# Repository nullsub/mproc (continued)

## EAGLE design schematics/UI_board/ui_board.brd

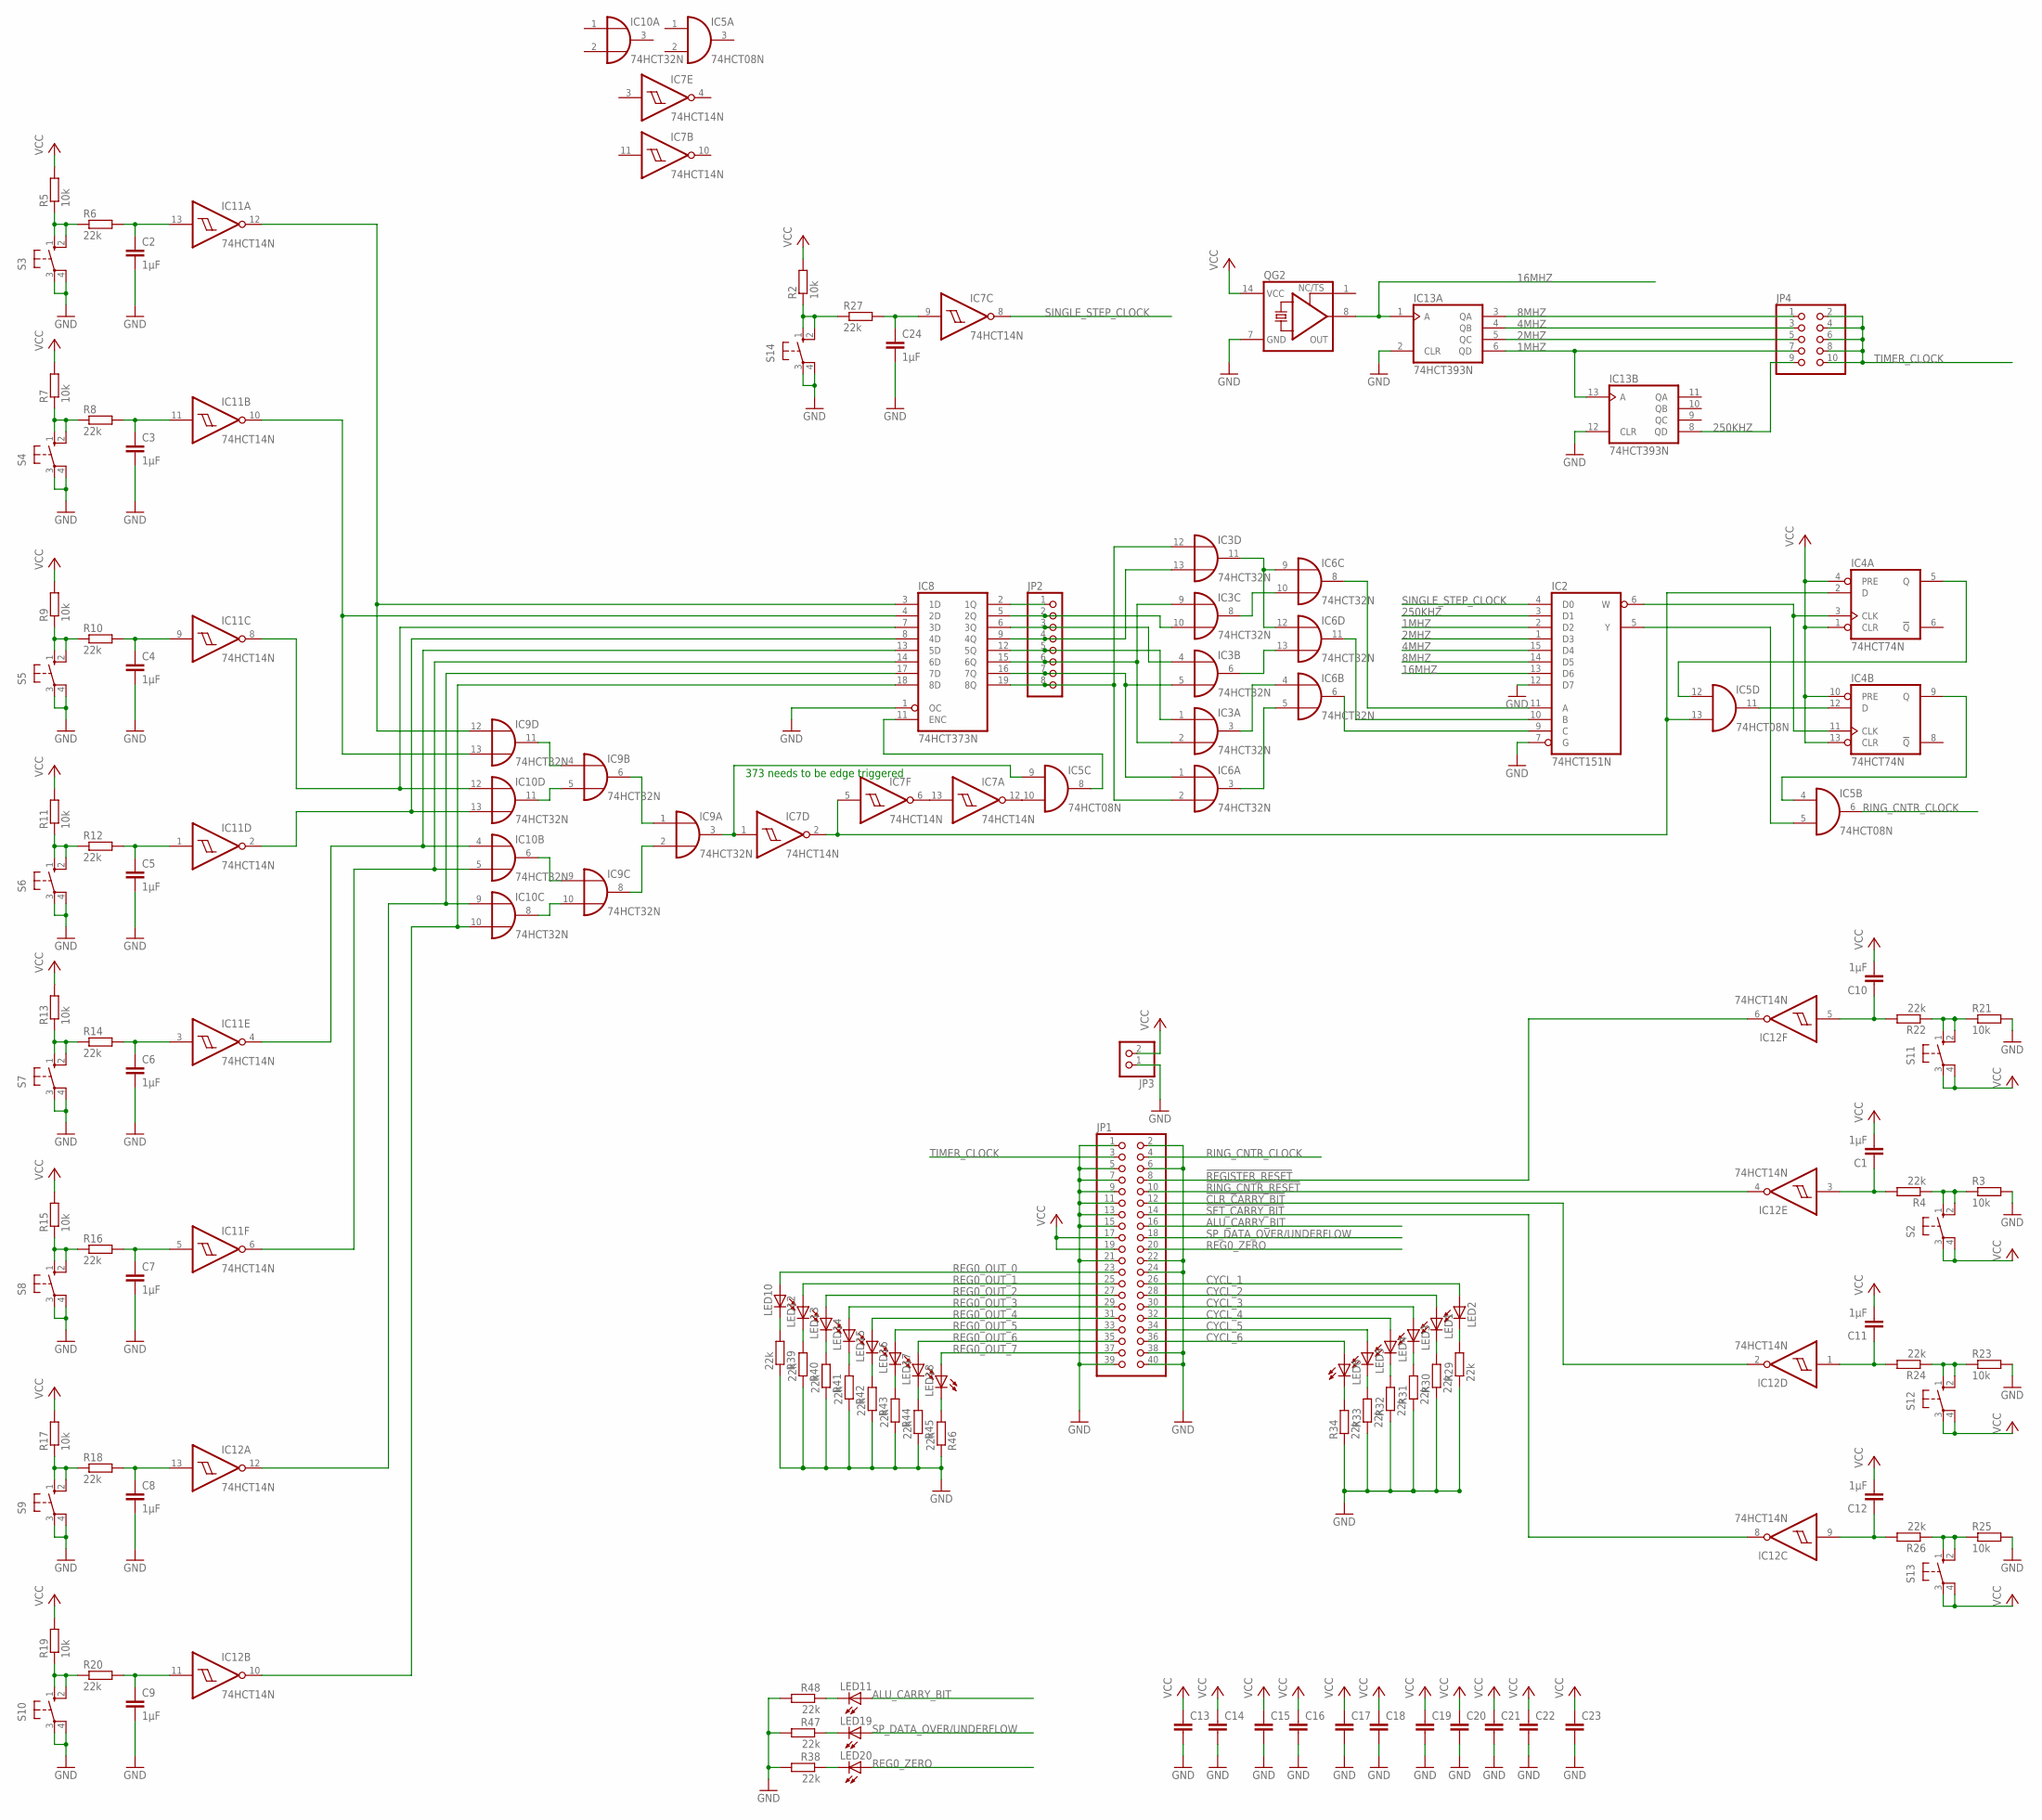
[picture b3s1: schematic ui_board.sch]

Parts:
C1, C2, C3, C4, C5, C6, C7, C8, C9, C10, C11, C12, C24: 1µF; C025-024X044
C13, C14, C15, C16, C17, C18, C19, C20, C21, C22, C23: C-EUC1206; C1206
IC2: 74HCT151N; DIL16
IC3, IC6, IC9, IC10: 74HCT32N; DIL14
IC4: 74HCT74N; DIL14
IC5: 74HCT08N; DIL14
IC7, IC11, IC12: 74HCT14N; DIL14
IC8: 74HCT373N; DIL20
IC13: 74HCT393N; DIL14
JP1: PINHD-2X20; 2X20
JP2: PINHD-1X8; 1X08
JP3: PINHD-1X2; 1X02
JP4: PINHD-2X5; 2X05
LED1, LED2, LED3, LED4, LED5, LED6, LED10, LED11, LED12, LED13, LED14, LED15, LED16, LED17, LED18, LED19, LED20: LED3MM
QG2: XO-14; DIL14S
R2, R3, R5, R7, R9, R11, R13, R15, R17, R19, R21, R23, R25: 10k; R1206
R4, R6, R8, R10, R12, R14, R16, R18, R20, R22, R24, R26, R27, R29, R30, R31, R32, R33, R34, R38, R39, R40, R41, R42, R43, R44, R45, R46, R47, R48: 22k; R1206
S2, S3, S4, S5, S6, S7, S8, S9, S10, S11, S12, S13, S14: 10-XX; B3F-10XX

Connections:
1MHZ: IC2.2 (D2), IC13.6 (QD), IC13.13 (A), JP4.7
2MHZ: IC2.1 (D3), IC13.5 (QC), JP4.5
4MHZ: IC2.15 (D4), IC13.4 (QB), JP4.3
8MHZ: IC2.14 (D5), IC13.3 (QA), JP4.1
16MHZ: IC2.13 (D6), IC13.1 (A), QG2.8 (OUT)
250KHZ: IC2.3 (D1), IC13.8 (QD), JP4.9
!CLR_CARRY_BIT: IC12.2 (O), JP1.12
!REGISTER_RESET: IC12.6 (O), JP1.8
!RING_CNTR_RESET: IC12.4 (O), JP1.10
!SET_CARRY_BIT: IC12.8 (O), JP1.14
ALU_CARRY_BIT: JP1.16, LED11.A
CHANGE_CLOCK_SELECT: IC5.9 (I0), IC7.1 (I), IC9.3 (O)
CHANGE_CLOCK_SELECT1: IC8.3 (1D), IC9.12 (I0), IC11.12 (O)
CHANGE_CLOCK_SELECT2: IC8.4 (2D), IC9.13 (I1), IC11.10 (O)
CHANGE_CLOCK_SELECT3: IC8.7 (3D), IC10.12 (I0), IC11.8 (O)
CHANGE_CLOCK_SELECT5: IC8.13 (5D), IC10.4 (I0), IC11.4 (O)
CHANGE_CLOCK_SELECT6: IC8.14 (6D), IC10.5 (I1), IC11.6 (O)
CHANGE_CLOCK_SELECT7: IC8.17 (7D), IC10.9 (I0), IC12.12 (O)
CHANGE_CLOCK_SELECT8: IC8.18 (8D), IC10.10 (I1), IC12.10 (O)
CYCL_1: JP1.26, LED2.A
CYCL_2: JP1.28, LED1.A
CYCL_3: JP1.30, LED3.A
CYCL_4: JP1.32, LED4.A
CYCL_5: JP1.34, LED5.A
CYCL_6: JP1.36, LED6.A
GND: C2.2, C3.2, C4.2, C5.2, C6.2, C7.2, C8.2, C9.2, C13.2, C14.2, C15.2, C16.2, C17.2, C18.2, C19.2, C20.2, C21.2, C22.2, C23.2, C24.2, IC2.7 (G), IC2.8 (GND), IC2.12 (D7), IC3.7 (GND), IC4.7 (GND), IC5.7 (GND), IC6.7 (GND), IC7.7 (GND), IC8.1 (OC), IC8.10 (GND), IC9.7 (GND), IC10.7 (GND), IC11.7 (GND), IC12.7 (GND), IC13.2 (CLR), IC13.7 (GND), IC13.12 (CLR), JP1.1, JP1.2, JP1.5, JP1.6, JP1.7, JP1.9, JP1.11, JP1.13, JP1.15, JP1.21, JP1.22, JP1.24, JP1.38, JP1.39, JP1.40, JP3.1, QG2.7 (GND), R3.2, R21.2, R23.2, R25.2, R29.1, R30.1, R31.1, R32.1, R33.1, R34.1, R38.2, R39.1, R40.1, R41.1, R42.1, R43.1, R44.1, R45.1, R46.1, R47.2, R48.2, S3.3, S3.4 (P1), S4.3, S4.4 (P1), S5.3, S5.4 (P1), S6.3, S6.4 (P1), S7.3, S7.4 (P1), S8.3, S8.4 (P1), S9.3, S9.4 (P1), S10.3, S10.4 (P1), S14.3, S14.4 (P1)
unnamed: IC4.9 (Q), IC5.4 (I0)
unnamed: R2.1, R27.1, S14.1 (S), S14.2 (S1)
unnamed: IC4.12 (D), IC5.11 (O)
unnamed: IC2.6 (W), IC4.3 (CLK), IC4.11 (CLK)
unnamed: IC2.10 (B), IC6.11 (O)
unnamed: IC8.2 (1Q), JP2.1
unnamed: IC4.5 (Q), IC5.12 (I0)
unnamed: IC7.6 (O), IC7.13 (I)
unnamed: IC4.2 (D), IC5.13 (I1), IC7.2 (O), IC7.5 (I)
unnamed: IC2.11 (A), IC6.8 (O)
unnamed: IC3.11 (O), IC6.9 (I0), IC6.12 (I0)
unnamed: IC2.9 (C), IC6.6 (O)
unnamed: R5.1, R6.1, S3.1 (S), S3.2 (S1)
unnamed: C2.1, IC11.13 (I), R6.2
unnamed: R7.1, R8.1, S4.1 (S), S4.2 (S1)
unnamed: LED20.K (C), R38.1
unnamed: IC3.6 (O), IC6.13 (I1)
unnamed: IC3.10 (I1), IC8.5 (2Q), JP2.2
unnamed: R3.1, R4.1, S2.1 (S), S2.2 (S1)
unnamed: IC3.13 (I1), IC8.9 (4Q), JP2.4
unnamed: IC3.1 (I0), IC8.12 (5Q), JP2.5
unnamed: IC3.2 (I1), IC3.9 (I0), IC8.15 (6Q), JP2.6
unnamed: IC3.5 (I1), IC6.1 (I0), IC8.16 (7Q), JP2.7
unnamed: IC3.12 (I0), IC6.2 (I1), IC8.19 (8Q), JP2.8
unnamed: IC9.5 (I1), IC10.11 (O)
unnamed: IC9.4 (I0), IC9.11 (O)
unnamed: IC9.9 (I0), IC10.6 (O)
unnamed: IC9.10 (I1), IC10.8 (O)
unnamed: IC9.2 (I1), IC9.8 (O)
unnamed: IC9.1 (I0), IC9.6 (O)
unnamed: IC3.8 (O), IC6.10 (I1)
unnamed: IC3.3 (O), IC6.4 (I0)
unnamed: IC6.3 (O), IC6.5 (I1)
unnamed: C3.1, IC11.11 (I), R8.2
unnamed: R9.1, R10.1, S5.1 (S), S5.2 (S1)
unnamed: C4.1, IC11.9 (I), R10.2
unnamed: R11.1, R12.1, S6.1 (S), S6.2 (S1)
unnamed: C5.1, IC11.1 (I), R12.2
unnamed: R13.1, R14.1, S7.1 (S), S7.2 (S1)
unnamed: C6.1, IC11.3 (I), R14.2
unnamed: R15.1, R16.1, S8.1 (S), S8.2 (S1)
unnamed: C7.1, IC11.5 (I), R16.2
unnamed: R17.1, R18.1, S9.1 (S), S9.2 (S1)
unnamed: C8.1, IC12.13 (I), R18.2
unnamed: R19.1, R20.1, S10.1 (S), S10.2 (S1)
unnamed: C9.1, IC12.11 (I), R20.2
unnamed: C1.1, IC12.3 (I), R4.2
unnamed: IC8.8 (4D), IC10.13 (I1), IC11.2 (O)
unnamed: R21.1, R22.1, S11.1 (S), S11.2 (S1)
unnamed: C10.1, IC12.5 (I), R22.2
unnamed: R23.1, R24.1, S12.1 (S), S12.2 (S1)
unnamed: C11.1, IC12.1 (I), R24.2
unnamed: R25.1, R26.1, S13.1 (S), S13.2 (S1)
unnamed: C12.1, IC12.9 (I), R26.2
unnamed: C24.1, IC7.9 (I), R27.2
unnamed: LED10.K (C), R39.2
unnamed: LED12.K (C), R40.2
unnamed: LED13.K (C), R41.2
unnamed: LED2.K (C), R29.2
unnamed: LED1.K (C), R30.2
unnamed: LED3.K (C), R31.2
unnamed: LED4.K (C), R32.2
unnamed: LED5.K (C), R33.2
unnamed: LED6.K (C), R34.2
unnamed: IC5.10 (I1), IC7.12 (O)
unnamed: LED14.K (C), R42.2
unnamed: LED15.K (C), R43.2
unnamed: LED16.K (C), R44.2
unnamed: LED17.K (C), R45.2
unnamed: LED18.K (C), R46.2
unnamed: LED19.K (C), R47.1
unnamed: LED11.K (C), R48.1
unnamed: IC3.4 (I0), IC8.6 (3Q), JP2.3
unnamed: IC5.8 (O), IC8.11 (ENC)
REG0_OUT_0: JP1.23, LED10.A
REG0_OUT_1: JP1.25, LED12.A
REG0_OUT_2: JP1.27, LED13.A
REG0_OUT_3: JP1.29, LED14.A
REG0_OUT_4: JP1.31, LED15.A
REG0_OUT_5: JP1.33, LED16.A
REG0_OUT_6: JP1.35, LED17.A
REG0_OUT_7: JP1.37, LED18.A
REG0_ZERO: JP1.20, LED20.A
RING_CNTR_CLOCK: IC5.6 (O), JP1.4
SELECTED_CLOCK: IC2.5 (Y), IC5.5 (I1)
SINGLE_STEP_CLOCK: IC2.4 (D0), IC7.8 (O)
SP_DATA_OVER/UNDERFLOW: JP1.18, LED19.A
TIMER_CLOCK: JP1.3, JP4.2, JP4.4, JP4.6, JP4.8, JP4.10
VCC: C1.2, C10.2, C11.2, C12.2, C13.1, C14.1, C15.1, C16.1, C17.1, C18.1, C19.1, C20.1, C21.1, C22.1, C23.1, IC2.16 (VCC), IC3.14 (VCC), IC4.1 (CLR), IC4.4 (PRE), IC4.10 (PRE), IC4.13 (CLR), IC4.14 (VCC), IC5.14 (VCC), IC6.14 (VCC), IC7.14 (VCC), IC8.20 (VCC), IC9.14 (VCC), IC10.14 (VCC), IC11.14 (VCC), IC12.14 (VCC), IC13.14 (VCC), JP1.17, JP1.19, JP3.2, QG2.14 (VCC), R2.2, R5.2, R7.2, R9.2, R11.2, R13.2, R15.2, R17.2, R19.2, S2.3, S2.4 (P1), S11.3, S11.4 (P1), S12.3, S12.4 (P1), S13.3, S13.4 (P1)

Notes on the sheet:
373 needs to be edge triggered

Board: 2 copper layers, 114 parts (42 on the bottom side), 115 nets, no tracks yet.

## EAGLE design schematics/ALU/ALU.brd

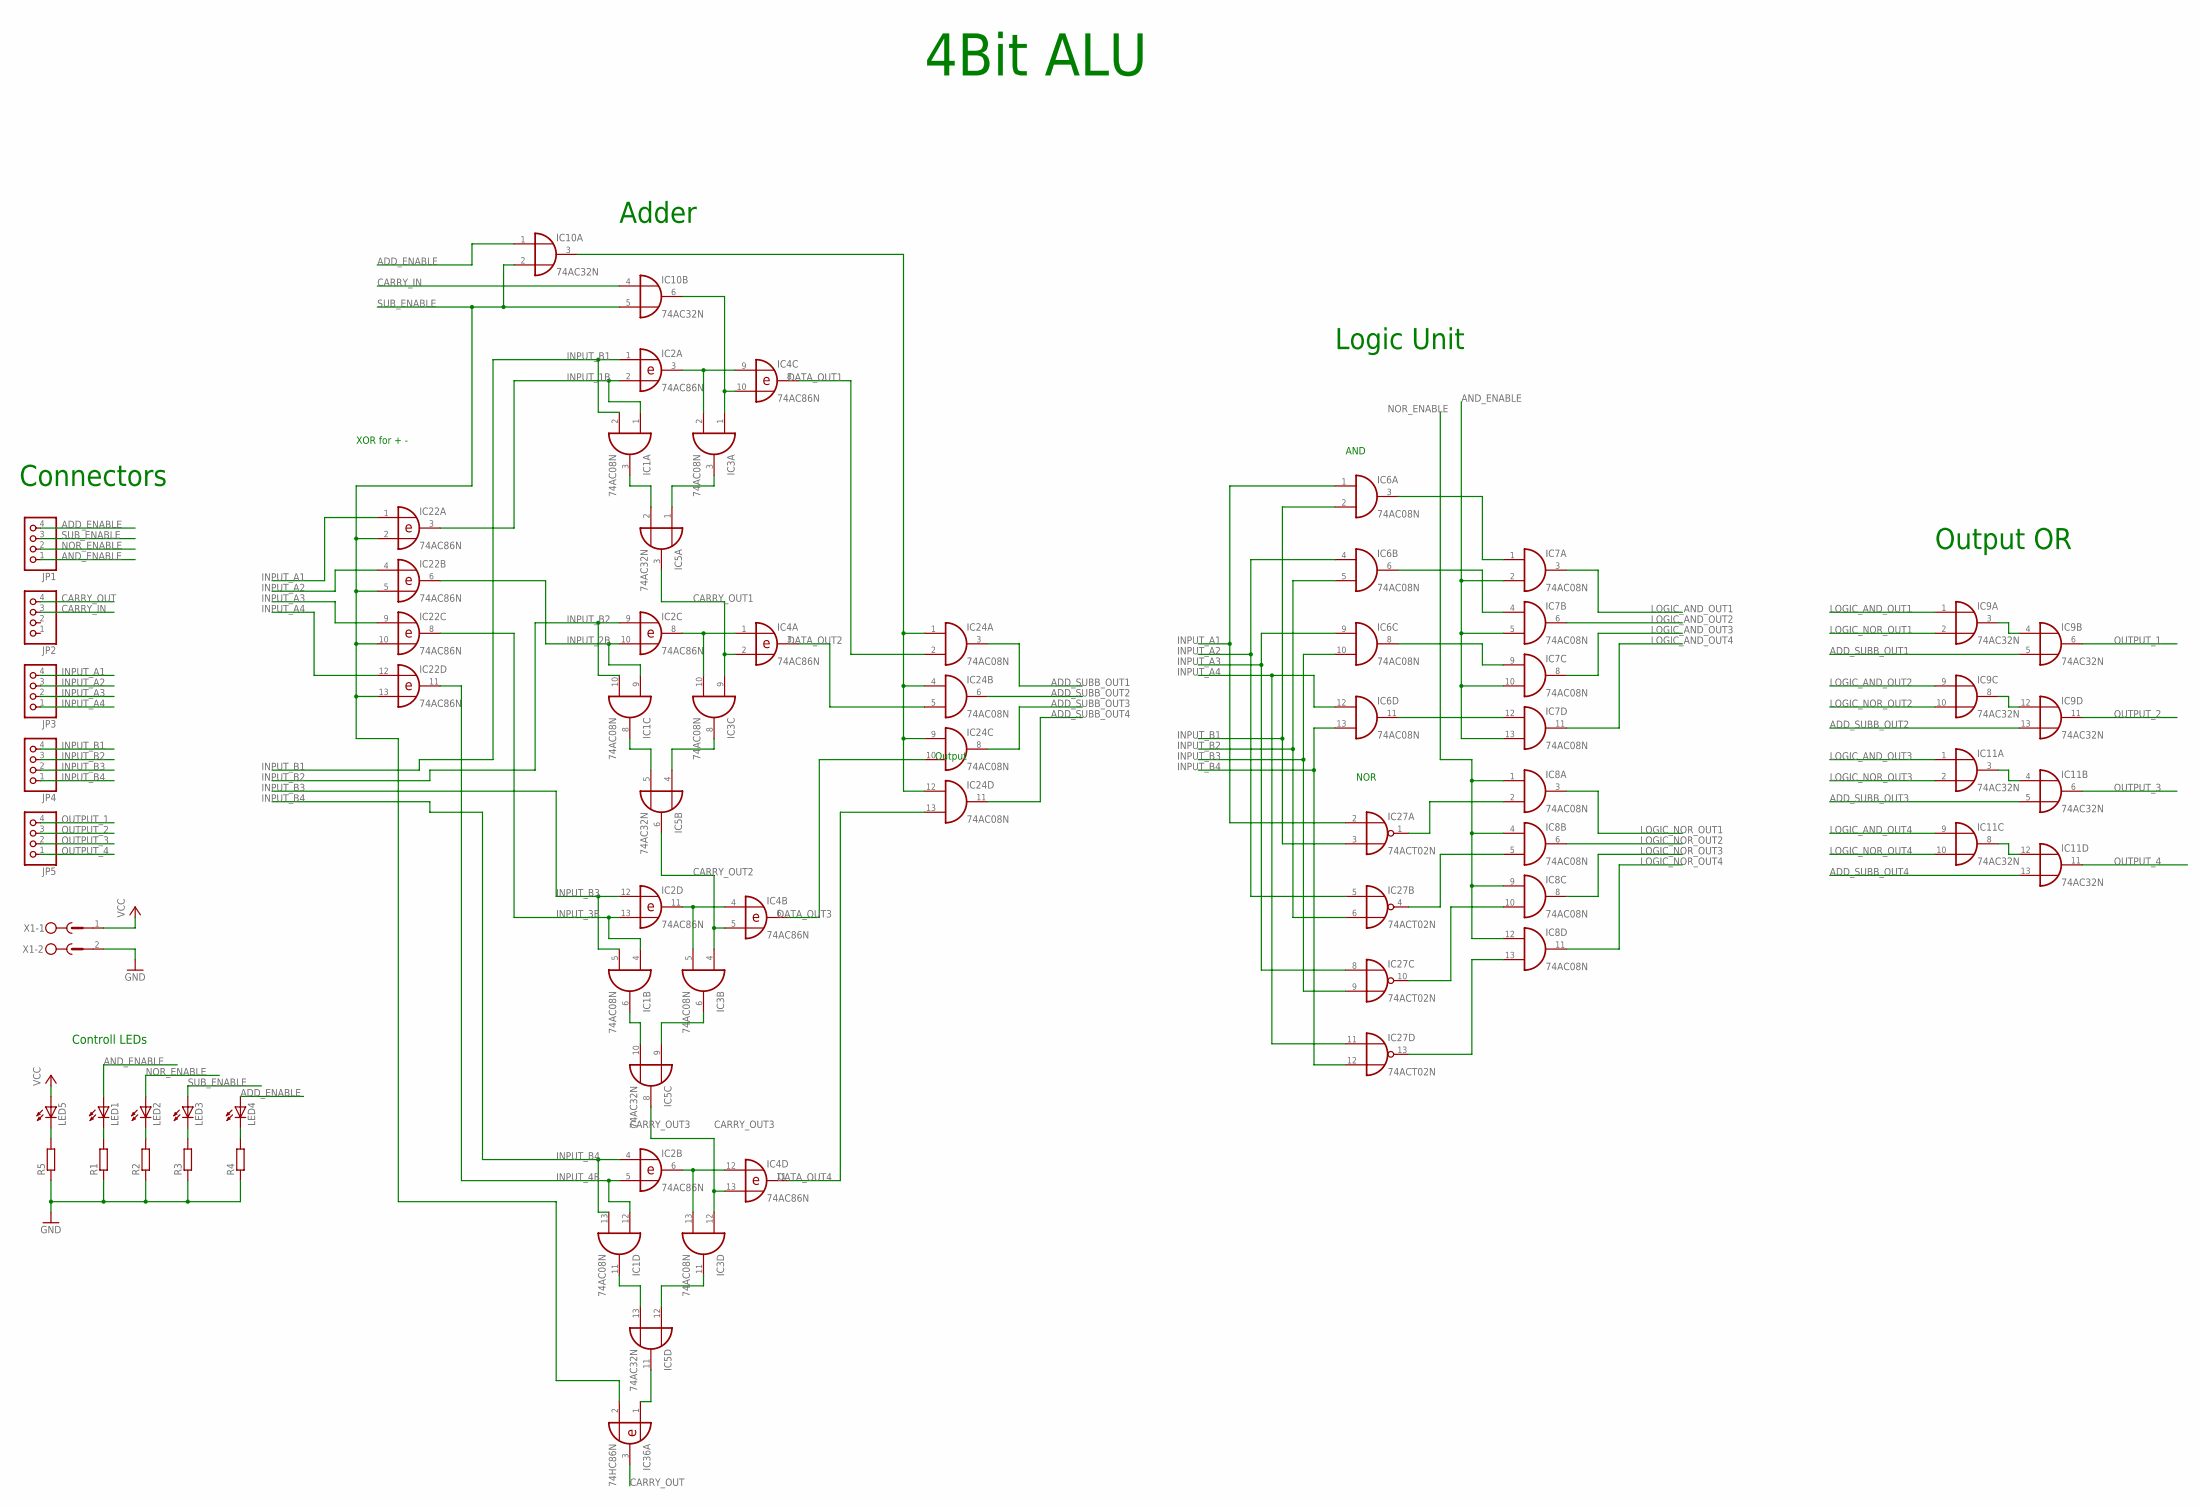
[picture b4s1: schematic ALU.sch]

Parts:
IC1, IC3, IC6, IC7, IC8, IC24: 74AC08N; DIL14
IC2, IC4, IC22: 74AC86N; DIL14
IC5, IC9, IC10, IC11: 74AC32N; DIL14
IC27: 74ACT02N; DIL14
IC36: 74HC86N; DIL14
JP1, JP2, JP3, JP4, JP5: PINHD-1X4; 1X04
LED1, LED2, LED3, LED4, LED5: LED5MM
R1, R2, R3, R4, R5: R-EU_0204/5; 0204/5
X1: MSTBV2

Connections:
ADD_ENABLE: IC10.1 (I0), JP1.4, LED4.A
ADD_SUBB_OUT1: IC9.5 (I1), IC24.3 (O)
ADD_SUBB_OUT2: IC9.13 (I1), IC24.6 (O)
ADD_SUBB_OUT3: IC11.5 (I1), IC24.8 (O)
ADD_SUBB_OUT4: IC11.13 (I1), IC24.11 (O)
ADD_SUB_ENABLE: IC10.3 (O), IC24.1 (I0), IC24.4 (I0), IC24.9 (I0), IC24.12 (I0)
AND_ENABLE: IC7.2 (I1), IC7.5 (I1), IC7.10 (I1), IC7.13 (I1), JP1.1, LED1.A
CARRY_IN: IC10.4 (I0), JP2.3
CARRY_OUT: IC36.3 (O), JP2.4
CARRY_OUT1: IC3.9 (I0), IC4.2 (I1), IC5.3 (O)
CARRY_OUT2: IC3.4 (I0), IC4.5 (I1), IC5.6 (O)
CARRY_OUT3: IC3.12 (I0), IC4.13 (I1), IC5.8 (O)
DATA_OUT1: IC4.8 (O), IC24.2 (I1)
DATA_OUT2: IC4.3 (O), IC24.5 (I1)
DATA_OUT3: IC4.6 (O), IC24.10 (I1)
DATA_OUT4: IC4.11 (O), IC24.13 (I1)
GND: IC1.7 (GND), IC2.7 (GND), IC3.7 (GND), IC4.7 (GND), IC5.7 (GND), IC6.7 (GND), IC7.7 (GND), IC8.7 (GND), IC9.7 (GND), IC10.7 (GND), IC11.7 (GND), IC22.7 (GND), IC24.7 (GND), IC27.7 (GND), IC36.7 (GND), R1.1, R2.1, R3.1, R4.1, R5.1, X1.2
INPUT_1B: IC1.1 (I0), IC2.2 (I1), IC22.3 (O)
INPUT_2B: IC1.9 (I0), IC2.10 (I1), IC22.6 (O)
INPUT_3B: IC1.4 (I0), IC2.13 (I1), IC22.8 (O)
INPUT_4B: IC1.12 (I0), IC2.5 (I1), IC22.11 (O)
INPUT_A1: IC6.1 (I0), IC22.1 (I0), IC27.2 (I0), JP3.4
INPUT_A2: IC6.4 (I0), IC22.4 (I0), IC27.5 (I0), JP3.3
INPUT_A3: IC6.9 (I0), IC22.9 (I0), IC27.8 (I0), JP3.2
INPUT_A4: IC6.12 (I0), IC22.12 (I0), IC27.11 (I0), JP3.1
INPUT_B1: IC1.2 (I1), IC2.1 (I0), IC6.2 (I1), IC27.3 (I1), JP4.4
INPUT_B2: IC1.10 (I1), IC2.9 (I0), IC6.5 (I1), IC27.6 (I1), JP4.3
INPUT_B3: IC1.5 (I1), IC2.12 (I0), IC6.10 (I1), IC27.9 (I1), JP4.2
INPUT_B4: IC1.13 (I1), IC2.4 (I0), IC6.13 (I1), IC27.12 (I1), JP4.1
LOGIC_AND_OUT1: IC7.3 (O), IC9.1 (I0)
LOGIC_AND_OUT2: IC7.6 (O), IC9.9 (I0)
LOGIC_AND_OUT3: IC7.8 (O), IC11.1 (I0)
LOGIC_AND_OUT4: IC7.11 (O), IC11.9 (I0)
LOGIC_NOR_OUT1: IC8.3 (O), IC9.2 (I1)
LOGIC_NOR_OUT2: IC8.6 (O), IC9.10 (I1)
LOGIC_NOR_OUT3: IC8.8 (O), IC11.2 (I1)
LOGIC_NOR_OUT4: IC8.11 (O), IC11.10 (I1)
unnamed: IC1.3 (O), IC5.2 (I1)
unnamed: IC3.3 (O), IC5.1 (I0)
unnamed: IC2.3 (O), IC3.2 (I1), IC4.9 (I0)
unnamed: IC3.8 (O), IC5.4 (I0)
unnamed: IC1.8 (O), IC5.5 (I1)
unnamed: IC2.8 (O), IC3.10 (I1), IC4.1 (I0)
unnamed: IC3.6 (O), IC5.9 (I0)
unnamed: IC1.6 (O), IC5.10 (I1)
unnamed: IC2.11 (O), IC3.5 (I1), IC4.4 (I0)
unnamed: IC3.11 (O), IC5.12 (I0)
unnamed: IC1.11 (O), IC5.13 (I1)
unnamed: IC2.6 (O), IC3.13 (I1), IC4.12 (I0)
unnamed: IC9.3 (O), IC9.4 (I0)
unnamed: IC9.8 (O), IC9.12 (I0)
unnamed: IC11.3 (O), IC11.4 (I0)
unnamed: IC11.8 (O), IC11.12 (I0)
unnamed: LED1.K (C), R1.2
unnamed: LED2.K (C), R2.2
unnamed: IC6.6 (O), IC7.4 (I0)
unnamed: IC6.8 (O), IC7.9 (I0)
unnamed: IC6.3 (O), IC7.1 (I0)
unnamed: IC6.11 (O), IC7.12 (I0)
unnamed: LED3.K (C), R3.2
unnamed: IC8.5 (I1), IC27.4 (O)
unnamed: IC8.10 (I1), IC27.10 (O)
unnamed: IC8.13 (I1), IC27.13 (O)
unnamed: IC8.2 (I1), IC27.1 (O)
unnamed: LED4.K (C), R4.2
unnamed: LED5.K (C), R5.2
unnamed: IC3.1 (I0), IC4.10 (I1), IC10.6 (O)
NOR_ENABLE: IC8.1 (I0), IC8.4 (I0), IC8.9 (I0), IC8.12 (I0), JP1.2, LED2.A
OUTPUT_1: IC9.6 (O), JP5.4
OUTPUT_2: IC9.11 (O), JP5.3
OUTPUT_3: IC11.6 (O), JP5.2
OUTPUT_4: IC11.11 (O), JP5.1
SUB_ENABLE: IC10.2 (I1), IC10.5 (I1), IC22.2 (I1), IC22.5 (I1), IC22.10 (I1), IC22.13 (I1), IC36.2 (I1), JP1.3, LED3.A
VCC: IC1.14 (VCC), IC2.14 (VCC), IC3.14 (VCC), IC4.14 (VCC), IC5.14 (VCC), IC6.14 (VCC), IC7.14 (VCC), IC8.14 (VCC), IC9.14 (VCC), IC10.14 (VCC), IC11.14 (VCC), IC22.14 (VCC), IC24.14 (VCC), IC27.14 (VCC), IC36.14 (VCC), LED5.A, X1.1
______________: IC5.11 (O), IC36.1 (I0)

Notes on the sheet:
Output
Adder
Logic Unit
AND
NOR
4Bit ALU
Output OR
Connectors
XOR for + -
Controll LEDs

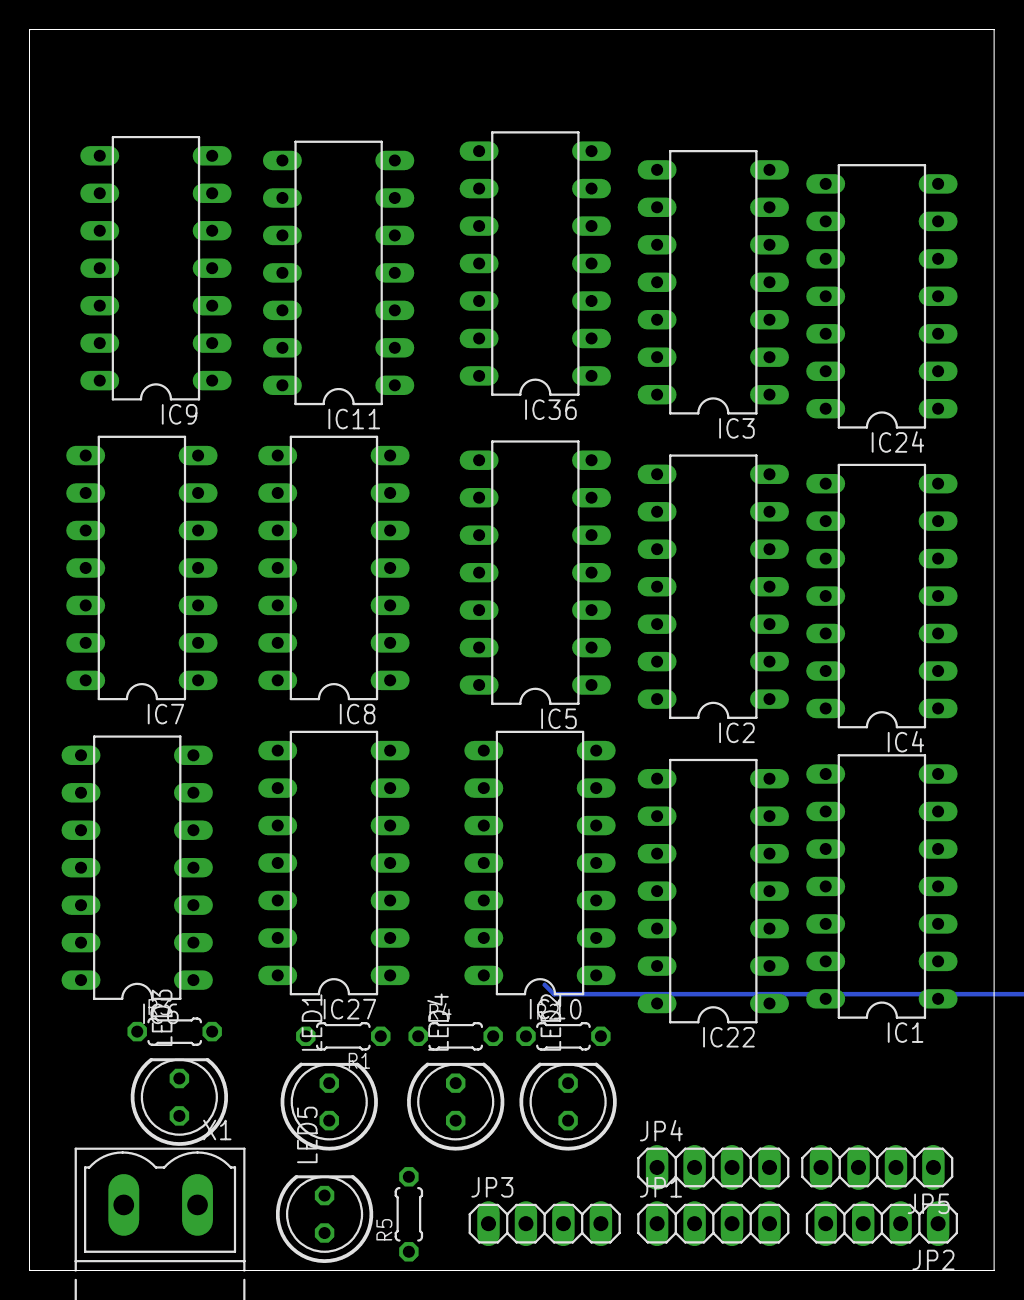
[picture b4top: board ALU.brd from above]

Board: 2 copper layers, 65.4 x 84.1 mm, 31 parts (0 on the bottom side), 75 nets.

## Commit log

2012-09-08 fixed typo
2012-09-13 changed the ISA(rm MOVC..). Implemented changes in assembler and emulator
2012-09-13 cleaned up assembler.c
2012-09-13 cleaned emulator.c
2012-09-13 added schematics
2012-09-13 changed dr to br. Bankregister sounds better than Dateregister.
2012-09-13 fixed define BUG: only one define was saved - added some memory management.
2012-10-14 added some docs(pdf)
2013-01-22 cleaned up.
2013-01-25 fixed LOW() and HIGH() bug. It was not working for normal base-10 integers
2013-01-26 updated Architecture. Make I/O mem mapped.
    changed the formatting of the code a bit
2013-01-26 reimplemented the opcode decoder.
    Still lots to be done
2013-01-26 changed JMP instruction. Use direct-immediate instead of offset operands
    This is easier to implement both in the compiler and in hardware since no 16-bit addition has to be done
2013-01-28 added a doc for the a binary counter used for the SP and PC.
2013-01-28 fixed operand decoder table. Use binary counter chip for the SP and PC.
    Lots of small changes.
2013-01-31 Finished opcode decoder. Changed ISA
    Changed STR and LDA instruction.
    Added new COUNT_BR instruction.
    COUNT_BR is not yet added to the assembler/emulator
2013-01-31 finalized design. I do not think I will change the instructions much more
2013-01-31 implement the design changes in the emulator and assembler
2013-01-31 Add I/O registers. Plus some small optimizations
2013-01-31 fix part-numbering. Created Board File - a bit large
2013-02-08 scale down the *brd. started the layout
2013-02-09 converted the mproc manual to LaTeX. Moved some files around.
2013-07-10 cleanup docs
2013-07-10 improve arch-design:
    rename BR register to PTR,
    rename COUNT_BR to PTR_ADD
    allow ofsets for PTR_ADD
2013-07-10 support offset address for JMP instruction
2013-07-12 add SAVE_LR and RET instructions to the docs
2013-07-13 implement SAVE_LR, RET, CALL
    does not yet work
2013-07-13 fix JMP(C/Z) bug. works
2013-07-13 cleanup. works.
2013-07-13 clean code
2013-08-09 add test structure. math test not yet implemented
2013-08-10 fix comparison bug. compare pointer not content!
2013-08-10 rename cmd->cmd_name to cmd->name
2013-08-10 add timeout to test script
2013-08-10 switch JMP arguments. JMP regA, regB equals to pc_high = regA, pc_low = regB
2013-08-12 fix math test. now 16bit add and subtract work
2013-08-12 cleanup emulator
2013-08-12 docs: fix implementation table.
2013-08-12 implement SET_PTR instruction
2013-08-14 fix readme
2013-08-14 schematic: implemented JMP offset instruction.
2013-08-15 implement PTR_ADD instruction. All instruction are now implemented!
2013-08-15 clean up schematic. next up is Instruction fetch & decode
2013-08-16 add fetch cycle
2013-08-23 fix offset commands JMP and ADD_PTR
2013-08-23 remove trailing whitespace
2013-08-24 remove opcode variable in argtable
2013-08-24 reorganize arg order. reg0, number is now encoded with 0x00
2013-08-25 add second byte load of instruction fetch.
2013-08-26 reorder arguments. decoding is now easier
2013-08-26 add two byte cmd decoder
2013-08-30 implement SAVE_LR/RET structure. LR register needs to be added.
2013-09-02 add LR register. All instructions are now implemented.
2013-09-04 finish ringcounter
2013-09-04 add led library
2013-09-06 add proper connectors
2013-09-06 remove leds. I will make a interface board with them
2013-09-11 add capacitors. Needs still some more..
2013-09-11 remove autorouter file
2013-09-12 add fanout comment.
2013-09-13 routing: it now fits on a 200x200mm board
2013-09-13 add nor gate to save space
2013-09-15 add dsn file for autorouting
2013-09-15 make brd file smaller
2013-09-15 optimize component count
2013-09-16 remove 2 more chips
2013-09-16 add UI board schematic
2013-09-20 changed register chips to 74xx374
2013-09-21 forgot it
2013-09-24 regroup
2013-10-01 optimize chip count :)
2013-10-02 start routing
2013-10-03 start ui board layout
2013-10-06 fix. gonna try to reduce cycles to 8 per instruction now
2013-10-07 got rid of two cycles! finetuning next
2013-10-20 soldered ui bord
2014-01-08 clean up docs and schematic. no functional changes
2014-01-08 add run_tests for assembler
2014-01-23 support paths with filenames
    fileending must be *.asm
2014-01-24 fix ui_bord. seems to work
2014-01-25 finished and tested ui-board.
    I Didnt check all clocks. 16Mhz, 4Mhz and the single_clock work
2014-01-25 finished COntrolUnit. Not much left to do
2014-01-30 improve layout
2014-03-10 fix latex docs
2014-04-15 renumber schematic parts
2014-04-25 fix WRITE_TO_DBUS signal
2014-04-26 optimize part count
2014-04-27 add ackermann function to tests
2014-04-27 add STR and LDR varianst with auto-postincrement.
    remove PTR_ADD instruction. usually increment by 1 is enough for most needs.
2014-05-11 feature freeze. I will now solder the Control Unit
2018-12-26 suport .include command in assembler
2018-12-27 small fixes
2018-12-27 throw error on duplicate .defines
2018-12-30 allow nested includes. uses separate preprocessor
2018-12-30 expand lib with uart_println
2018-12-31 detect invalid encodings
2019-02-03 begin wokr on 16 bit ackermannfunction
2019-09-12 add some files
2019-09-12 add travis ci tests
2019-09-12 add travis to readme
